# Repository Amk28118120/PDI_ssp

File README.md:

Power and Data Tranfer (PDI)
Two identical PCB's are being used for testing. The schematic PDI_v1 is of one PCB.
The sizing of passive components is as follows - 
1) Rlim - 42.2kΩ
2) CdVdT = 2.2nF
3) R(IMON) = 43kΩ
4) C1 - 100-nF to 220-nF decoupling capacitors
5) R5 ,R6-  Use 1-kΩ to 10-kΩ pull-up and pull-down resistors for enable lines to limit noise currents in theses lines during transient events.
6) R7,R8 -10Ω
7) R2 = 120

The rationale for sizing is given in the document -https://docs.google.com/document/d/1Z6xQF2i3oRSEwMOCmPyrtTIQfxgxBp68ftvw1PFQKHI/edit?tab=t.0#heading=h.l0r2exo0l2pc

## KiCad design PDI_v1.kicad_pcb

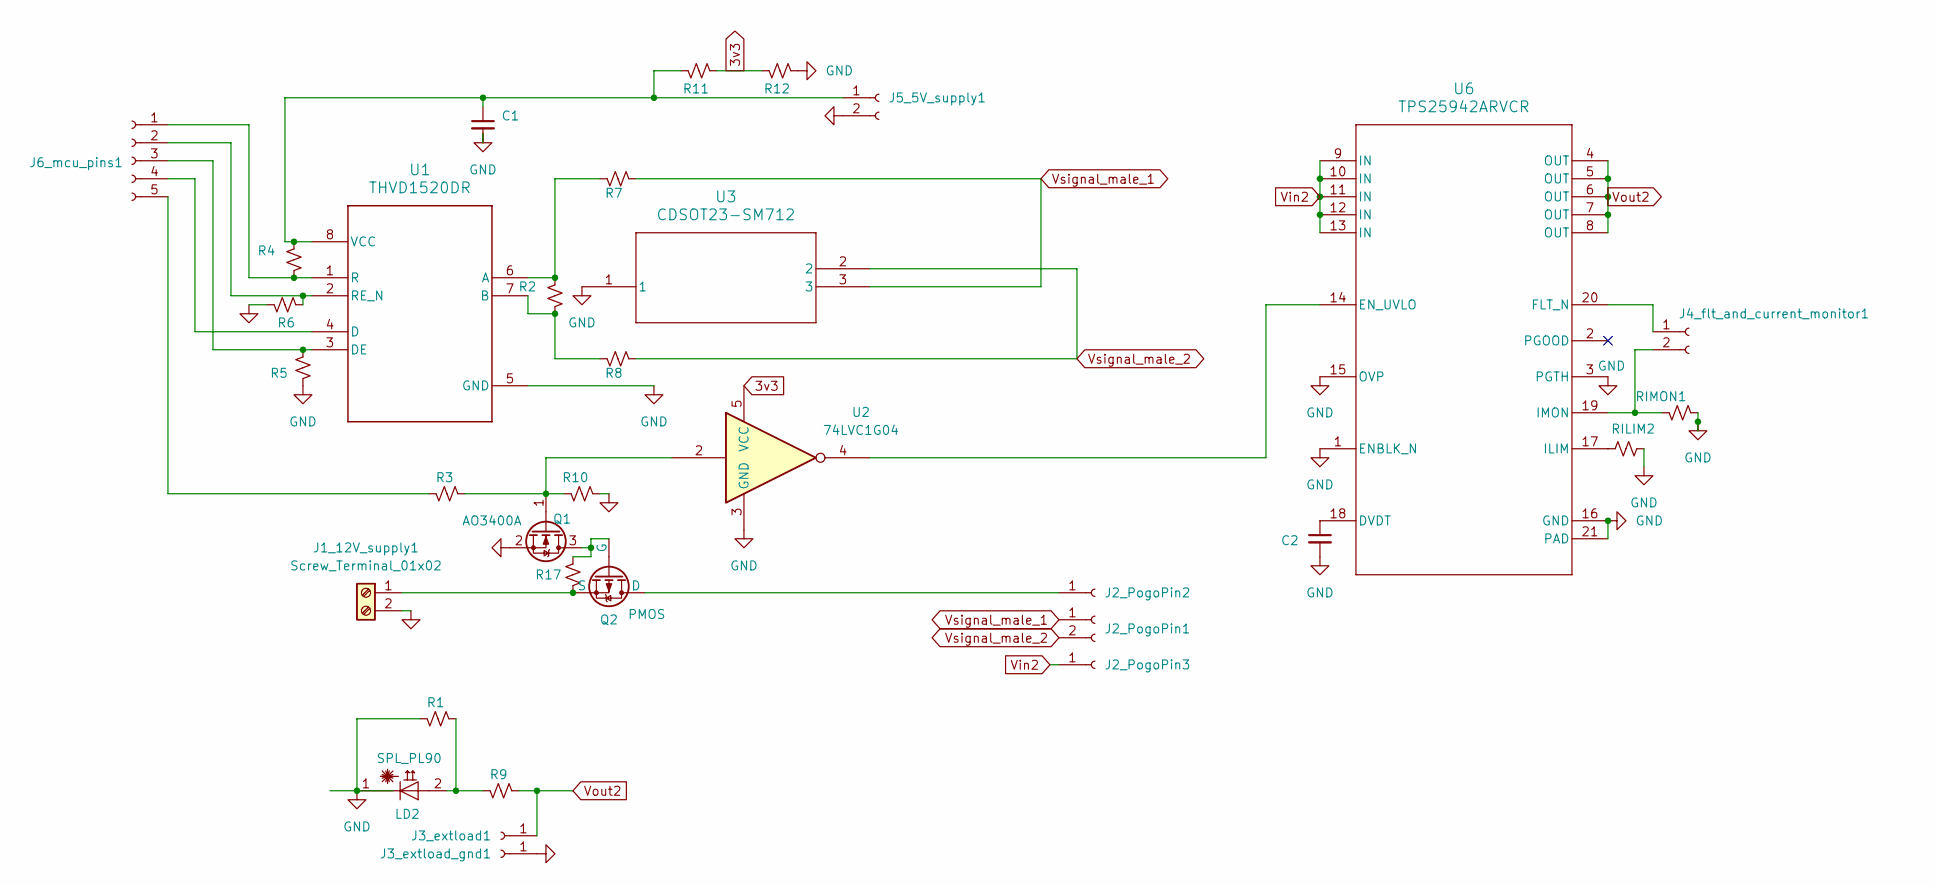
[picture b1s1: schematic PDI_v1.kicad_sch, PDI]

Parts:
C1, C2: C_Small; C_0805_2012Metric_Pad1.18x1.45mm_HandSolder
J1_12V_supply1: Screw_Terminal_01x02; TerminalBlock_MaiXu_MX126-5.0-02P_1x02_P5.00mm
J2_PogoPin1, J4_flt_and_current_monitor1: Conn_01x04_Socket; PinHeader_1x02_P1.00mm_Vertical
J2_PogoPin2, J2_PogoPin3, J3_extload1, J3_extload_gnd1: Conn_01x04_Socket; PinHeader_1x01_P1.00mm_Vertical
J5_5V_supply1: Conn_01x02_Socket; PinHeader_1x02_P1.00mm_Vertical
J6_mcu_pins1: Conn_01x05_Socket; PinHeader_1x05_P1.00mm_Vertical
LD2: SPL_PL90; LED_D3.0mm
Q1: AO3400A; SOT-23
Q2: PMOS; SOT-23
R1, R2, R3, R4, R5, R6, R7, R8, R9, R10, R11, R12, R17: R_Small_US; R_0805_2012Metric_Pad1.20x1.40mm_HandSolder
RILIM2: R_Small_US; R_0805_2012Metric_Pad1.20x1.40mm_HandSolder
RIMON1: R_Small_US; R_0805_2012Metric_Pad1.20x1.40mm_HandSolder
U1: THVD1520DR; SOIC-8_3.9x4.9mm_P1.27mm
U2: 74LVC1G04; SOT-23-5_HandSoldering
U3: CDSOT23-SM712; SOT-23
U6: TPS25942ARVCR; QFN-20-1EP_3x4mm_P0.5mm_EP1.65x2.65mm

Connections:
3v3: R11.2, R12.1, U2.5 (VCC)
GND: C1.2, C2.2, J1_12V_supply1.2, J3_extload_gnd1.1, J5_5V_supply1.2, LD2.1 (C), Q1.2 (S), R1.1, R5.2, R6.1, R10.2, R12.2, RILIM2.2, RIMON1.2, U1.5 (GND), U2.3 (GND), U3.1, U6.1 (ENBLK_N), U6.3 (PGTH), U6.15 (OVP), U6.16 (GND), U6.21 (PAD)
unnamed: J1_12V_supply1.1, Q2.3 (S), R17.2
unnamed: J2_PogoPin2.1, Q2.1 (D)
unnamed: J4_flt_and_current_monitor1.1, U6.20 (FLT_N)
unnamed: J4_flt_and_current_monitor1.2, RIMON1.1, U6.19 (IMON)
unnamed: C1.1, J5_5V_supply1.1, R4.1, R11.1, U1.8 (VCC)
unnamed: J6_mcu_pins1.1, R4.2, U1.1 (R)
unnamed: J6_mcu_pins1.2, R6.2, U1.2 (RE_N)
unnamed: J6_mcu_pins1.3, R5.1, U1.3 (DE)
unnamed: J6_mcu_pins1.4, U1.4 (D)
unnamed: J6_mcu_pins1.5, R3.1
unnamed: LD2.2 (A), R1.2, R9.1
unnamed: Q1.3 (D), Q2.2 (G), R17.1
unnamed: Q1.1 (G), R3.2, R10.1, U2.2
unnamed: R2.1, R7.1, U1.6 (A)
unnamed: R2.2, R8.1, U1.7 (B)
unnamed: C2.1, U6.18 (DVDT)
unnamed: U2.4, U6.14 (EN_UVLO)
unnamed: RILIM2.1, U6.17 (ILIM)
Vin2: J2_PogoPin3.1, U6.9 (IN), U6.10 (IN), U6.11 (IN), U6.12 (IN), U6.13 (IN)
Vout2: J3_extload1.1, R9.2, U6.4 (OUT), U6.5 (OUT), U6.6 (OUT), U6.7 (OUT), U6.8 (OUT)
Vsignal_male_1: J2_PogoPin1.1, R7.2, U3.3
Vsignal_male_2: J2_PogoPin1.2, R8.2, U3.2

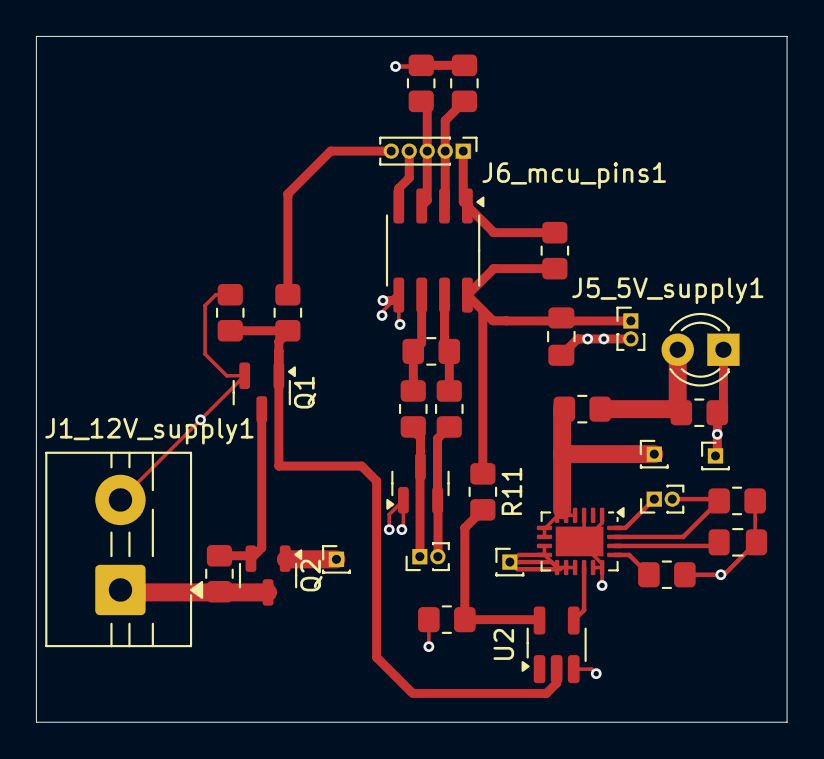
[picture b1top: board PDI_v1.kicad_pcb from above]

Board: 2 copper layers, 41.7 x 38.1 mm, 33 parts (0 on the bottom side), 24 nets.

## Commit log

2025-12-28 Add files via upload
    schematic and pcb design of one of the two identical pcbs used for testing data and power transfer
